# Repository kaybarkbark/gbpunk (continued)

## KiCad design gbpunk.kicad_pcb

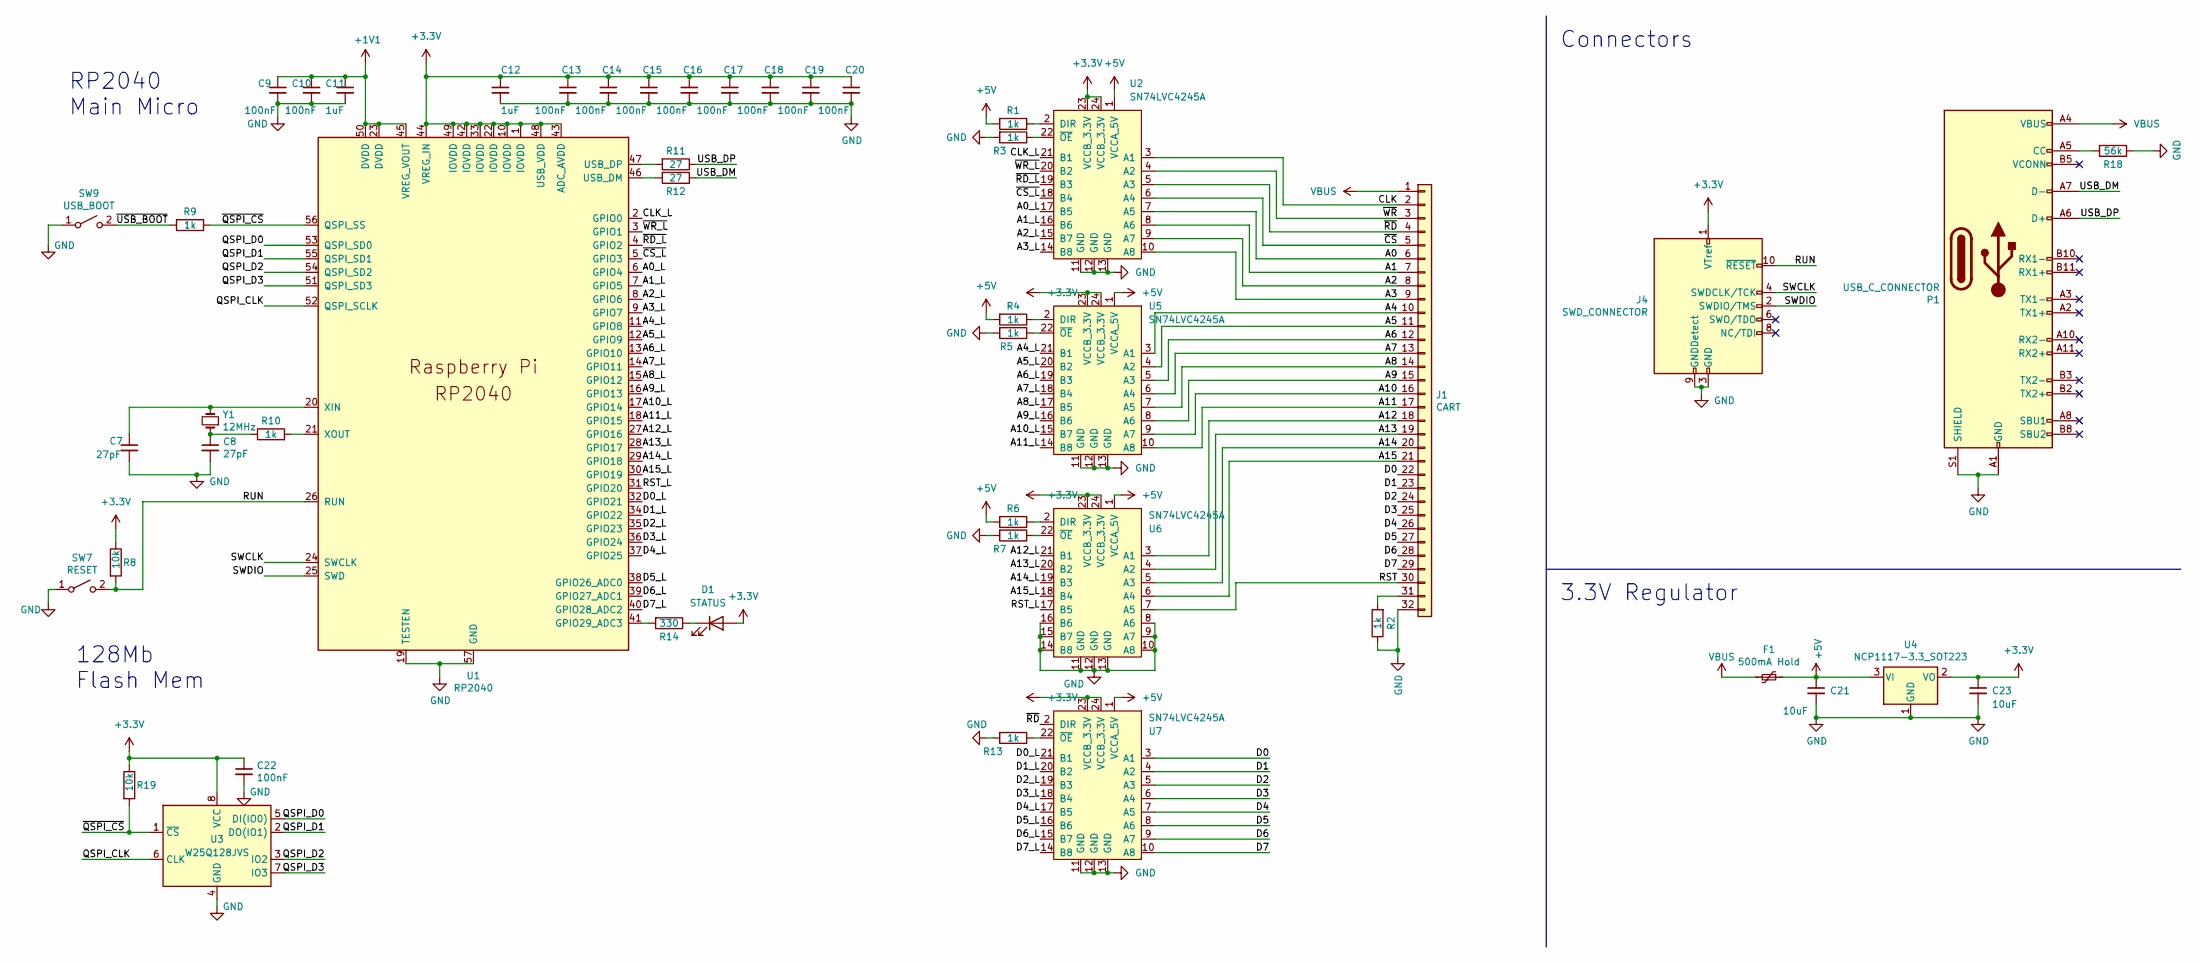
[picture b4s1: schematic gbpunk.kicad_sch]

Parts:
C7, C8: 27pF; C_0402_1005Metric_Pad0.74x0.62mm_HandSolder
C9, C10, C13, C14, C15, C16, C17, C18, C19, C20, C22: 100nF; C_0402_1005Metric_Pad0.74x0.62mm_HandSolder
C11, C12: 1uF; C_0805_2012Metric_Pad1.18x1.45mm_HandSolder
C21, C23: 10uF; C_1206_3216Metric_Pad1.33x1.80mm_HandSolder
D1: STATUS; LED_0603_1608Metric_Pad1.05x0.95mm_HandSolder
F1: 500mA Hold; Fuse_1206_3216Metric_Pad1.42x1.75mm_HandSolder
J1: CART; GameBoy_Cartridge_1x32_P1.50mm_Edge
J4: SWD_CONNECTOR; PinHeader_2x05_P1.27mm_Vertical_SMD
P1: USB_C_CONNECTOR; USB_C_Receptacle_HRO_TYPE-C-31-M-12
R1, R2, R3, R4, R5, R6, R7, R13: 1k; R_0603_1608Metric_Pad0.98x0.95mm_HandSolder
R8, R19: 10k; R_0402_1005Metric_Pad0.72x0.64mm_HandSolder
R9, R10: 1k; R_0402_1005Metric_Pad0.72x0.64mm_HandSolder
R11, R12: 27; R_0603_1608Metric_Pad0.98x0.95mm_HandSolder
R14: 330; R_0603_1608Metric_Pad0.98x0.95mm_HandSolder
R18: 56k; R_0402_1005Metric_Pad0.72x0.64mm_HandSolder
SW7: RESET; SW_SPST_EVPBF
SW9: USB_BOOT; SW_SPST_EVPBF
U1: RP2040; RP2040-QFN-56
U2, U5, U6, U7: SN74LVC4245A; TSSOP-24_4.4x7.8mm_P0.65mm
U3: W25Q128JVS; SOIC-8_5.23x5.23mm_P1.27mm
U4: NCP1117-3.3_SOT223; SOT-223-3_TabPin2
Y1: 12MHz; Crystal_HC52-8mm_Vertical

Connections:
+1V1: C9.1, C10.1, C11.1, U1.23 (DVDD), U1.45 (VREG_VOUT), U1.50 (DVDD)
+3.3V: C12.1, C13.1, C14.1, C15.1, C16.1, C17.1, C18.1, C19.1, C20.1, C22.1, C23.1, D1.2 (A), J4.1 (VTref), R8.1, R19.1, U1.1 (IOVDD), U1.10 (IOVDD), U1.22 (IOVDD), U1.33 (IOVDD), U1.42 (IOVDD), U1.43 (ADC_AVDD), U1.44 (VREG_IN), U1.48 (USB_VDD), U1.49 (IOVDD), U2.23 (VCCB_3.3V), U2.24 (VCCB_3.3V), U3.8 (VCC), U4.2 (VO), U5.23 (VCCB_3.3V), U5.24 (VCCB_3.3V), U6.23 (VCCB_3.3V), U6.24 (VCCB_3.3V), U7.23 (VCCB_3.3V), U7.24 (VCCB_3.3V)
+5V: C21.1, F1.1, R1.2, R4.2, R6.2, U2.1 (VCCA_5V), U4.3 (VI), U5.1 (VCCA_5V), U6.1 (VCCA_5V), U7.1 (VCCA_5V)
/A0: J1.6, U2.7 (A5)
/A0_L: U1.6 (GPIO4), U2.17 (B5)
/A1: J1.7, U2.8 (A6)
/A1_L: U1.7 (GPIO5), U2.16 (B6)
/A2: J1.8, U2.9 (A7)
/A2_L: U1.8 (GPIO6), U2.15 (B7)
/A3: J1.9, U2.10 (A8)
/A3_L: U1.9 (GPIO7), U2.14 (B8)
/A4: J1.10, U5.3 (A1)
/A4_L: U1.11 (GPIO8), U5.21 (B1)
/A5: J1.11, U5.4 (A2)
/A5_L: U1.12 (GPIO9), U5.20 (B2)
/A6: J1.12, U5.5 (A3)
/A6_L: U1.13 (GPIO10), U5.19 (B3)
/A7: J1.13, U5.6 (A4)
/A7_L: U1.14 (GPIO11), U5.18 (B4)
/A8: J1.14, U5.7 (A5)
/A8_L: U1.15 (GPIO12), U5.17 (B5)
/A9: J1.15, U5.8 (A6)
/A9_L: U1.16 (GPIO13), U5.16 (B6)
/A10: J1.16, U5.9 (A7)
/A10_L: U1.17 (GPIO14), U5.15 (B7)
/A11: J1.17, U5.10 (A8)
/A11_L: U1.18 (GPIO15), U5.14 (B8)
/A12: J1.18, U6.3 (A1)
/A12_L: U1.27 (GPIO16), U6.21 (B1)
/A13: J1.19, U6.4 (A2)
/A13_L: U1.28 (GPIO17), U6.20 (B2)
/A14: J1.20, U6.5 (A3)
/A14_L: U1.29 (GPIO18), U6.19 (B3)
/A15: J1.21, U6.6 (A4)
/A15_L: U1.30 (GPIO19), U6.18 (B4)
/CLK: J1.2, U2.3 (A1)
/CLK_L: U1.2 (GPIO0), U2.21 (B1)
/D0: J1.22, U7.3 (A1)
/D0_L: U1.32 (GPIO21), U7.21 (B1)
/D1: J1.23, U7.4 (A2)
/D1_L: U1.34 (GPIO22), U7.20 (B2)
/D2: J1.24, U7.5 (A3)
/D2_L: U1.35 (GPIO23), U7.19 (B3)
/D3: J1.25, U7.6 (A4)
/D3_L: U1.36 (GPIO24), U7.18 (B4)
/D4: J1.26, U7.7 (A5)
/D4_L: U1.37 (GPIO25), U7.17 (B5)
/D5: J1.27, U7.8 (A6)
/D5_L: U1.38 (GPIO26_ADC0), U7.16 (B6)
/D6: J1.28, U7.9 (A7)
/D6_L: U1.39 (GPIO27_ADC1), U7.15 (B7)
/D7: J1.29, U7.10 (A8)
/D7_L: U1.40 (GPIO28_ADC2), U7.14 (B8)
/QSPI_CLK: U1.52 (QSPI_SCLK), U3.6 (CLK)
/QSPI_D0: U1.53 (QSPI_SD0), U3.5 (DI(IO0))
/QSPI_D1: U1.55 (QSPI_SD1), U3.2 (DO(IO1))
/QSPI_D2: U1.54 (QSPI_SD2), U3.3 (IO2)
/QSPI_D3: U1.51 (QSPI_SD3), U3.7 (IO3)
/RST: J1.30, U6.7 (A5)
/RST_L: U1.31 (GPIO20), U6.17 (B5)
/RUN: J4.10 (~RESET), R8.2, SW7.2 (B), U1.26 (RUN)
/SWCLK: J4.4 (SWDCLK/TCK), U1.24 (SWCLK)
/SWDIO: J4.2 (SWDIO/TMS), U1.25 (SWD)
/USB_DM: P1.A7 (D-), R12.1
/USB_DP: P1.A6 (D+), R11.1
/~CS_L: U1.5 (GPIO3), U2.18 (B4)
/~CS: J1.5, U2.6 (A4)
/~QSPI_CS: R9.1, R19.2, U1.56 (QSPI_SS), U3.1 (~CS)
/~RD_L: U1.4 (GPIO2), U2.19 (B3)
/~RD: J1.4, U2.5 (A3), U7.2 (DIR)
/~USB_BOOT: R9.2, SW9.2 (B)
/~WR_L: U1.3 (GPIO1), U2.20 (B2)
/~WR: J1.3, U2.4 (A2)
GND: C7.2, C8.2, C9.2, C10.2, C11.2, C12.2, C13.2, C14.2, C15.2, C16.2, C17.2, C18.2, C19.2, C20.2, C21.2, C22.2, C23.2, J1.32, J4.3 (GND), J4.5 (GND), J4.9 (GNDDetect), P1.A1 (GND), P1.A12 (GND), P1.B1 (GND), P1.B12 (GND), P1.S1 (SHIELD), R2.1, R3.2, R5.2, R7.2, R13.2, R18.2, SW7.1 (A), SW9.1 (A), U1.19 (TESTEN), U1.57 (GND), U2.11 (GND), U2.12 (GND), U2.13 (GND), U3.4 (GND), U4.1 (GND), U5.11 (GND), U5.12 (GND), U5.13 (GND), U6.8 (A6), U6.9 (A7), U6.10 (A8), U6.11 (GND), U6.12 (GND), U6.13 (GND), U6.14 (B8), U6.15 (B7), U6.16 (B6), U7.11 (GND), U7.12 (GND), U7.13 (GND)
unnamed: C7.1, U1.20 (XIN), Y1.2
unnamed: C8.1, R10.1, Y1.1
unnamed: D1.1 (K), R14.1
unnamed: J1.31, R2.2
unnamed: P1.A5 (CC), R18.1
unnamed: R1.1, U2.2 (DIR)
unnamed: R3.1, U2.22 (~OE)
unnamed: R4.1, U5.2 (DIR)
unnamed: R5.1, U5.22 (~OE)
unnamed: R6.1, U6.2 (DIR)
unnamed: R7.1, U6.22 (~OE)
unnamed: R10.2, U1.21 (XOUT)
unnamed: R11.2, U1.47 (USB_DP)
unnamed: R12.2, U1.46 (USB_DM)
unnamed: R13.1, U7.22 (~OE)
unnamed: R14.2, U1.41 (GPIO29_ADC3)
VBUS: F1.2, J1.1, P1.A4 (VBUS), P1.A9 (VBUS), P1.B4 (VBUS), P1.B9 (VBUS)

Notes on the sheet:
Connectors
3.3V Regulator
RP2040 Main Micro
128Mb Flash Mem

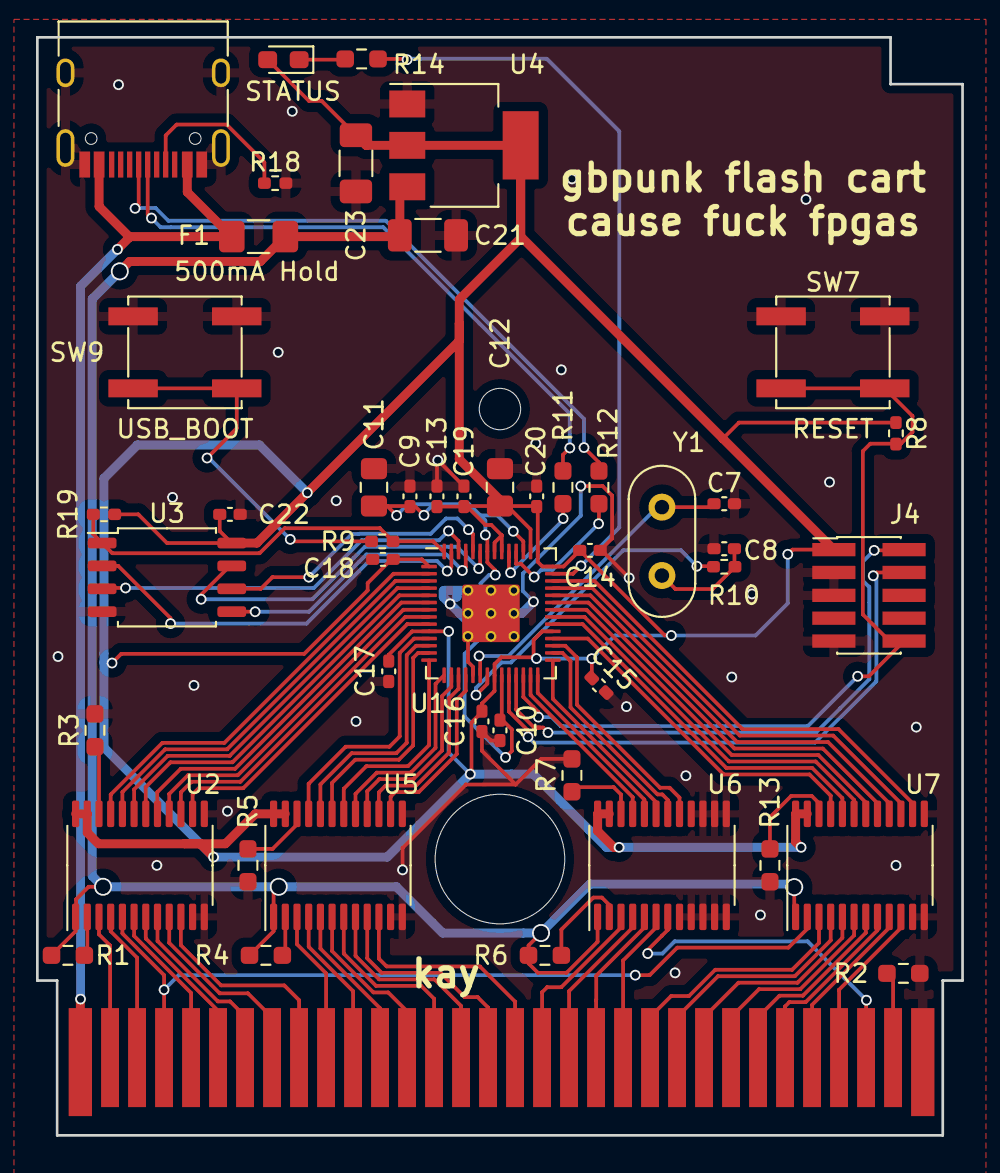
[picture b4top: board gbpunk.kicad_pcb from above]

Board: 2 copper layers, 51.4 x 61.0 mm, 50 parts (0 on the bottom side), 91 nets.

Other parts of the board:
MK1: DNF; MountingHole_7.2mm
MK2: DNF; MountingHole_2.3mm

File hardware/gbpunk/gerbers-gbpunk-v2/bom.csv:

Designation,Designator,Footprint,LCSC Part Number
100nF,"C20,C13,C17,C14,C22,C16,C15,C19,C18,C10,C9",C_0402_1005Metric_Pad0.74x0.62mm_HandSolder,C1525
SN74LVC4245A,"U7,U6,U2,U5",TSSOP-24_4.4x7.8mm_P0.65mm,C7859
1k,"R9,R10",R_0402_1005Metric_Pad0.72x0.64mm_HandSolder,C279981
1k,"R13,R6,R5,R7,R1,R2,R4,R3",R_0603_1608Metric_Pad0.98x0.95mm_HandSolder,C21190
10uF,"C21,C23",C_1206_3216Metric_Pad1.33x1.80mm_HandSolder,C13585
1uF,"C11,C12",C_0805_2012Metric_Pad1.18x1.45mm_HandSolder,C28323
27R,"R11,R12",R_0603_1608Metric_Pad0.98x0.95mm_HandSolder,C25190
10k,"R19,R8",R_0402_1005Metric_Pad0.72x0.64mm_HandSolder,C25744
USB_BOOT,SW9,SW_SPST_EVPBF,C318884
USB_C_CONNECTOR,P1,USB_C_Receptacle_HRO_TYPE-C-31-M-12,C165948
27pF,"C8,C7",C_0402_1005Metric_Pad0.74x0.62mm_HandSolder,C1557
56k,"R18,R15",R_0402_1005Metric_Pad0.72x0.64mm_HandSolder,C25796
W25Q128JVS,U3,SOIC-8_5.23x5.23mm_P1.27mm,C97521
RESET,SW7,SW_SPST_EVPBF,C318884
NCP1117-3.3_SOT223,U4,SOT-223-3_TabPin2,C6186
RP2040,U1,RP2040-QFN-56,C2040
STATUS,D1,LED_0603_1608Metric_Pad1.05x0.95mm_HandSolder,C72043
330R,R14,R_0603_1608Metric_Pad0.98x0.95mm_HandSolder,C23138

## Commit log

2022-09-01 sent to fab
2022-09-13 working on getting IRQ working:
2022-10-05 need an interposer to measure timings
2023-01-16 updated interposer
2023-01-17 Dumping works
2023-01-24 organizing
2023-01-25 can dump out what looks like an entire mbc5
2023-02-07 it worked maybe? it will bankswitch proper now
2023-02-08 can read out files completely now
2023-02-19 kinda works
2023-02-20 fully supports ROM only carts
2023-02-20 Committing this before I start to mess with timings again
2023-02-21 the read speedups are complete, going to start messing with the filesystem
2023-02-21 added support for multiple files, made status file work
2023-02-28 fixed issues with the FAT and dumped out a ROM that is over 1MB
2023-02-28 BIG RESTRUCTURE - seperated gb into gb and cart. gb is for low level pin twiddling and cart is for cart - made the cart a static object so it can just be used anywhere - wrote in code for the functio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
2023-02-28 ok well it almost worked
2023-03-01 all the big mappers work
2023-03-02 working on an actual unit test framework that can be shared amongst all the carts
2023-03-03 wrote a banksw test
2023-03-04 sram rd wr wip
2023-03-04 unit tests work (except for SRAM writes) and the status file is way better
2023-03-05 SRAM hates me
2023-03-05 sram doesn't hate me I am just dumb
2023-03-06 huge cleanup of the awful disk stuff
2023-03-06 fixed a bug in the FAT chain generator where the terminating entries were getting created in the wrong place, started work on the gbcam interface
2023-03-08 can pull photos now
2023-03-12 gonna start messing with the filesystem driver, need a clean start
2023-03-13 WIP Add Variable FS
    Branching off because technically the original, static FS should have never fucking worked in the first place. The FAT chain is just straight up wrong
    ```
    00000200: ffff ffff 0000 0400 0500 0600 0700 0800 ................
    00000210: 0900 0a00 ffff 0000 0000 0000 0000 0000 ................
    ```
    The entry for the status.txt is 0x0000, completely invalid. Need to revert and fix that and do other tests.
2023-03-13 fixed a bug where the FAT chain got generated wrong on small files (1 cluster large)
2023-03-19 going slow now, swapped enums out for changeable file indexes
2023-03-19 organized and renamed some stuff, working on making the file sizes variable now
2023-03-19 the last of the enums are variables
2023-03-19 I think the variable fs just works now?
2023-03-19 seems like all the variable fs stuff is finally working
2023-03-20 cleaned up the disk stuff a lot and seperated it into two files
2023-03-24 Fixed mbc3 rom flashing but I do not know how
2023-03-25 Fixed mbc1, on to mbc2
2023-03-26 mbc2 fully working, should probably add bounds checking to all other carts to be safe
2023-03-27 gotta swap all the pins now :(
2023-03-27 big PCB reroute so the connector is not upside down
2023-03-28 wrote a python lib to decode game metadata from roms and dump to CSVs, should aid in finding cheap carts to test functionality with
2023-04-02 updated the board
2023-04-02 orderd boards for V2
2023-04-02 improvements to categorization script
2023-04-02 list of all the games I could find, mined for hardware capabilities
2023-04-03 turning gbcater into an actually useful library
2023-04-05 moved gbcater, added huc1 functionality. Remember to document huc1! nobody has
2023-04-05 huc3 works, same as huc1
2023-05-10 stuff
2023-06-28 added detection circuit and voltage switching for GBA/GB
2023-09-08 Support for different arm toolchain
    New arm toolchain on this machine took a shit and I needed to throw a bunch of externs everywhere
2025-10-13 updated hardware
2025-10-13 update build
2025-10-13 update build system
2026-03-27 need to double check but hardware rev looks good
2026-04-01 ready to start version 2.0. picking this project back up, technology and I have both progresses
2026-04-01 fuck microsoft
2026-04-01 oops
